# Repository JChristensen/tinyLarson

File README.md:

# Tiny Larson Scanner
https://github.com/JChristensen/tinyLarson  
README file  
Jack Christensen  
May-2019

## License
  
Tiny Larson Scanner by Jack Christensen is licensed under a [Creative Commons Attribution-ShareAlike 4.0 International License](http://creativecommons.org/licenses/by-sa/4.0/).

## Overview
This is just a fun project which is designed to utilize remaining capacity in old batteries while adding some decorative [Blinkenlights](https://en.wikipedia.org/wiki/Blinkenlights) to your shop or office.

Many battery-powered devices complain of low battery when there is still significant usable capacity left in the cells. Such cells can often power this circuit for many days or even a few weeks as the circuit only requires a few milliamperes and utilizes a boost regulator to maintain a constant supply voltage.

The circuit board fits on a dual AA cell holder and also has screw terminals for connection to other sources of power.

For more information, see the [firmware here](https://github.com/JChristensen/larson84).  
PC boards can be ordered from [OSH Park](https://oshpark.com/shared_projects/H8Wv3avv).  
A bill of materials is available at [Mouser Electronics](https://www.mouser.com/ProjectManager/ProjectDetail.aspx?AccessID=ef0590339b) and also in this repo.

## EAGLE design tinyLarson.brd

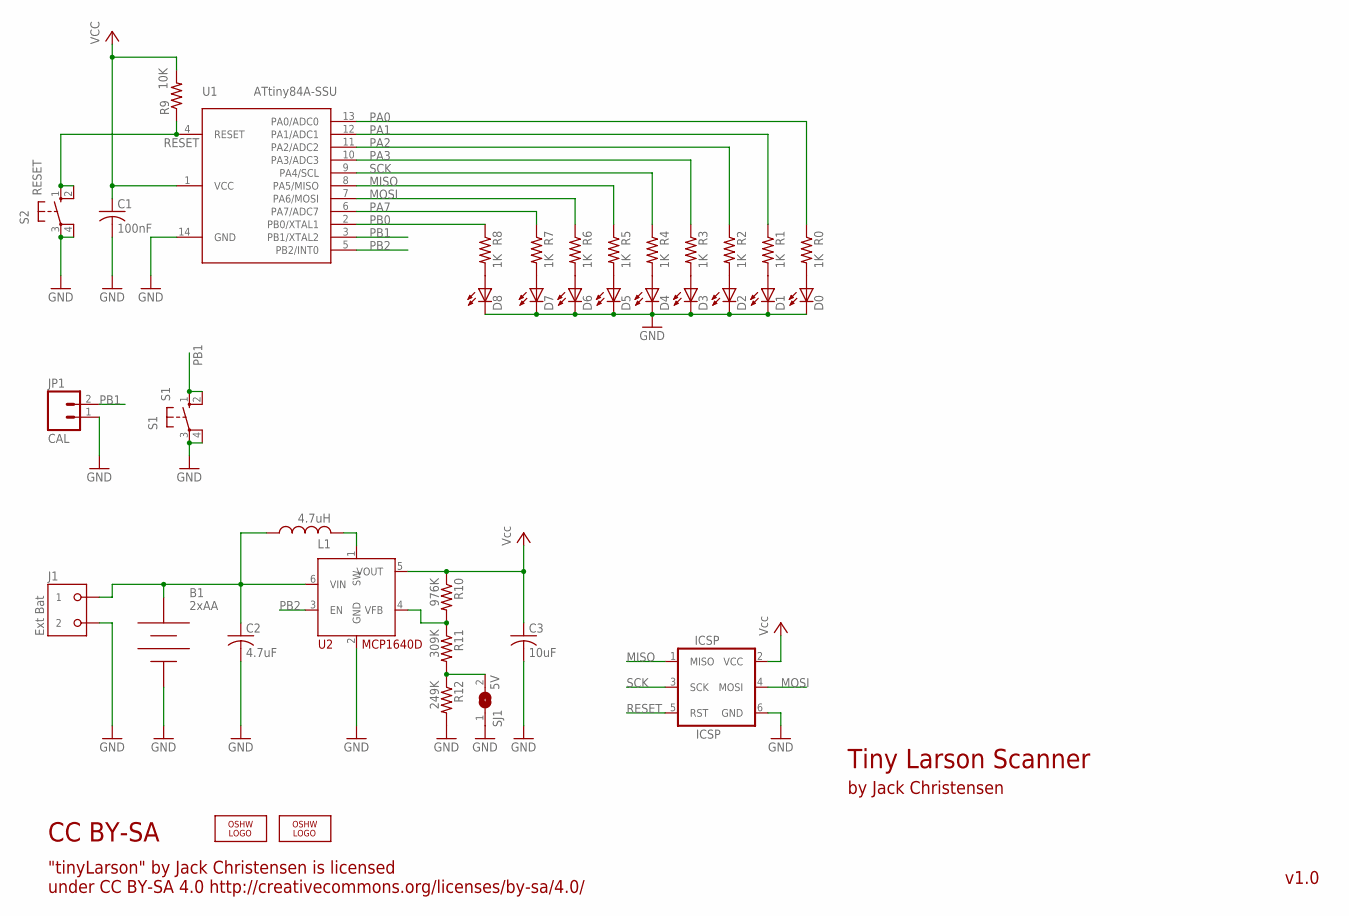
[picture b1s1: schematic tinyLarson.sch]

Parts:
B1: 2xAA; EAGLE-12BH321P-GR
C1: 100nF; M0805
C2: 4.7uF; M0805
C3: 10uF; M0805
D0, D1, D2, D3, D4, D5, D6: Yel; D0805A
D7: Yel; D0805
D8: Red; D0805
ICSP: ICSP; 2X3_LOCK
J1: Ext Bat; OST-TB-2-3.5MM
JP1: CAL; 1X02_LOCK
L1: 4.7uH; C1210K
LOGO1, LOGO2: OSHW_LOGO_8MILX0100-NT; OSHW_8X100_NOTEXT
R0, R1, R2, R3, R4, R5, R6, R7, R8: 1K; M0805
R9: 10K; M0805
R10: 976K; M0805
R11: 309K; M0805
R12: 249K; M0805
S1: S1; B3F-10XXOCT
S2: RESET; B3F-10XXOCT
SJ1: 5V; SJ
U1: ATtiny84A-SSU; SO14
U2: MCP1640D; SOT23-6

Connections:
GND: B1.NEG, C1.2, C2.2, C3.2, D0.K (C), D1.K (C), D2.K (C), D3.K (C), D4.K (C), D5.K (C), D6.K (C), D7.K (C), D8.K (C), ICSP.6 (GND), J1.P$2 (2), JP1.1, R12.2, S1.3, S1.4 (P1), S2.3, S2.4 (P1), SJ1.1, U1.14 (GND), U2.2 (GND)
MISO: ICSP.1 (MISO), R5.1, U1.8 (PA5/MISO)
MOSI: ICSP.4 (MOSI), R6.1, U1.7 (PA6/MOSI)
unnamed: R11.2, R12.1, SJ1.2
unnamed: R10.2, R11.1, U2.4 (VFB)
unnamed: D0.A, R0.2
unnamed: D1.A, R1.2
unnamed: D2.A, R2.2
unnamed: D3.A, R3.2
unnamed: L1.2, U2.1 (SW)
unnamed: D4.A, R4.2
unnamed: D5.A, R5.2
unnamed: D6.A, R6.2
unnamed: B1.POS, C2.1, J1.P$1 (1), L1.1, U2.6 (VIN)
unnamed: D7.A, R7.2
unnamed: D8.A, R8.2
PA0: R0.1, U1.13 (PA0/ADC0)
PA1: R1.1, U1.12 (PA1/ADC1)
PA2: R2.1, U1.11 (PA2/ADC2)
PA3: R3.1, U1.10 (PA3/ADC3)
PA7: R7.1, U1.6 (PA7/ADC7)
PB0: R8.1, U1.2 (PB0/XTAL1)
PB1: JP1.2, S1.1 (S), S1.2 (S1), U1.3 (PB1/XTAL2)
PB2: U1.5 (PB2/INT0), U2.3 (EN)
RESET: ICSP.5 (RST), R9.1, S2.1 (S), S2.2 (S1), U1.4 (RESET)
SCK: ICSP.3 (SCK), R4.1, U1.9 (PA4/SCL)
VCC: C1.1, C3.1, ICSP.2 (VCC), R9.2, R10.1, U1.1 (VCC), U2.5 (VOUT)

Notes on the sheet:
"tinyLarson" by Jack Christensen is licensed under CC BY-SA 4.0 http://creativecommons.org/licenses/by-sa/4.0/
CC BY-SA
Tiny Larson Scanner
by Jack Christensen
v1.0

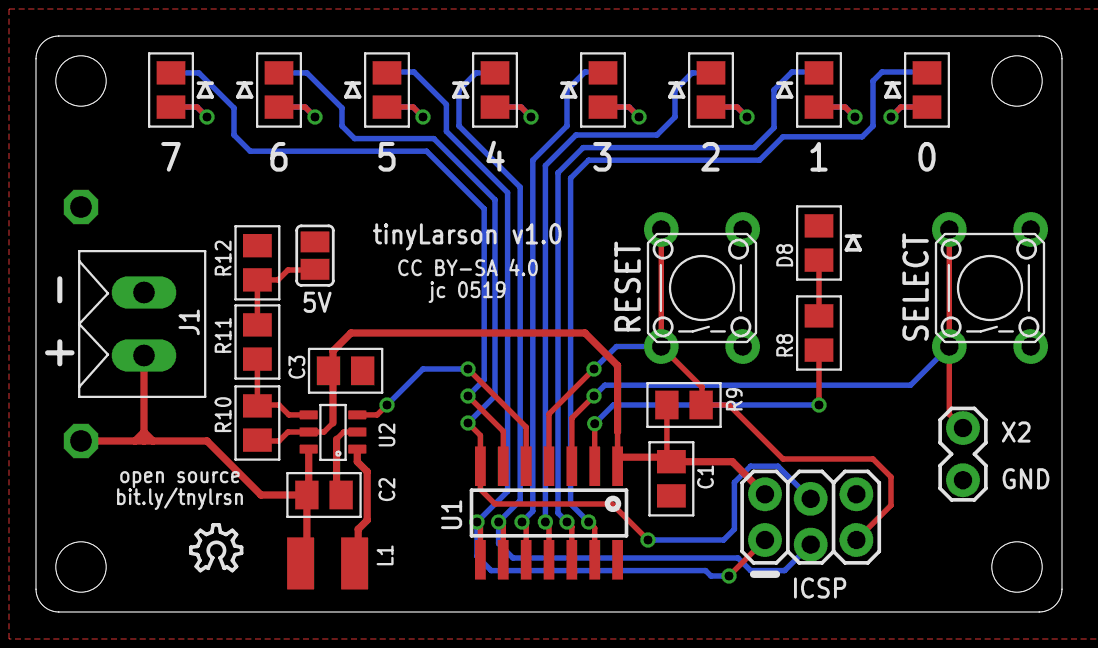
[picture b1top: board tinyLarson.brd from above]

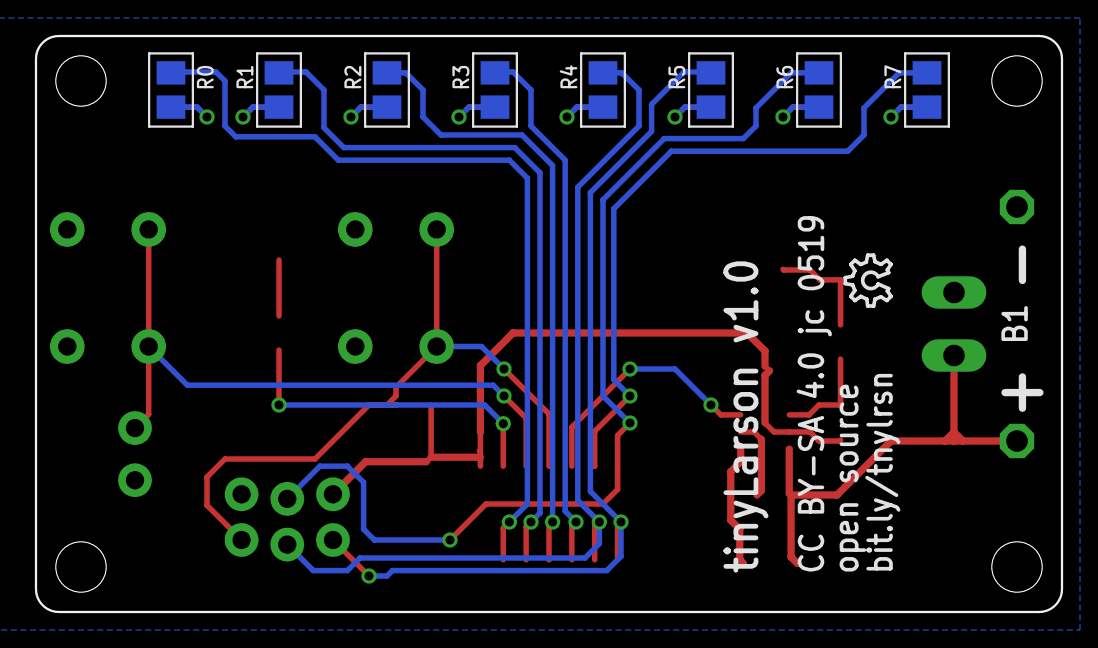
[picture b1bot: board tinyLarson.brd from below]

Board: 2 copper layers, 57.0 x 32.0 mm, 37 parts (10 on the bottom side), 27 nets.

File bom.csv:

Bill of Materials,,,,,
Tiny Larson Scanner,,,,,
by Jack Christensen,,,,,
May-2019,,,,,
https://www.mouser.com/ProjectManager/ProjectDetail.aspx?Acc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,,,,,
,,,,,
Part,Qty,Mouser #,Description,Mfr. #,Manufacturer
B1,1,12BH321P-GR,"Cylindrical Battery Contacts, Clips, Holders & Springs 2 ""AA"" PC LEADS BLK",12BH321P-GR,Eagle Plastic Devices
C1,1,581-08053C104K,Multilayer Ceramic Capacitors MLCC - SMD/SMT 25V .1uF X7R 0805 10%TOL,08053C104KAT2A,AVX
C2,1,963-EMK212ABJ475KG-T,Multilayer Ceramic Capacitors MLCC - SMD/SMT 0805 16VDC 4.7uF 10% X5R,EMK212ABJ475KG-T,Taiyo Yuden
C3,1,963-LMK212BJ106KG-T,Multilayer Ceramic Capacitors MLCC - SMD/SMT 10uF 10V X5R +/-10% 0805 Gen Purp,LMK212BJ106KG-T,Taiyo Yuden
D0-D7,8,859-LTST-C171KSKT,Standard LEDs - SMD Yellow Clear 587nm,LTST-C171KSKT,Lite-On
D8,1,859-LTST-C171KRKT,Standard LEDs - SMD Red Clear 55MCD,LTST-C171KRKT,Lite-On
J1,1,651-1984617,Fixed Terminal Blocks PT 1.5/2-3.5H 2POS HRZ 3.5mm SCREW,1984617,Phoenix Contact
L1,1,963-CBC3225T4R7MR,Fixed Inductors 1210 4.7uH 130mOhms +/-20% 1010mA HiCur,CBC3225T4R7MR,Taiyo Yuden
R0-R8,9,603-RC0805FR-071KL,Thick Film Resistors - SMD 1K OHM 1%,RC0805FR-071KL,Yageo
R10,1,660-RK73H2ATTD9763F,Thick Film Resistors - SMD 1/4W 976K OHM 1%,RK73H2ATTD9763F,KOA Speer
R11,1,660-RK73H2ATTD3093F,Thick Film Resistors - SMD 1/4W 309K OHM 1%,RK73H2ATTD3093F,KOA Speer
R12,1,660-RK73H2ATTD2493F,Thick Film Resistors - SMD 1/4W 249K OHM 1%,RK73H2ATTD2493F,KOA Speer
R9,1,603-RC0805FR-1310KL,Thick Film Resistors - SMD 10K OHM 1%,RC0805FR-1310KL,Yageo
S1-S2,2,653-B3F-1020,Tactile Switches 6X6 Flat 5mm Btn Force 100g w/o Grd,B3F-1020,Omron
U1,1,556-ATTINY84A-SSU,8-bit Microcontrollers - MCU 20MHz Ind. Grade,ATTINY84A-SSU,Microchip
U2,1,579-MCP1640DT-I/CHY,Switching Voltage Regulators 500 kHz 300 mA Syn Boost Converter,MCP1640DT-I/CHY,Microchip

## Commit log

2019-05-23 Initial commit.
2019-05-30 Add images.
2019-07-10 Add README, LICENSE, BOM, photo.
2023-09-04 Update schematic document number.

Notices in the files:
tinyLarson.brd:
CC BY-SA 4.0 jc 0519
parts and their libraries:
SparkFun: Licensing: CC v3.0 Share-Alike You are welcome to use this library for commercial purposes.
